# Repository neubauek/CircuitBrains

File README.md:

# CircuitBrains

## Deluxe
<br/>
https://kevinneubauer.com/projects/circuitbrains-deluxe/

Small form-factor 48-pin castellated pad module. Designed to allow an easy implementation of CircuitPython in maker/hacker projects without the bulk of a large breakout board.

Specs:
- Atmel ATSAMD51J19A Microcontroller (32-bit ARM Cortex M4)
- 8 MB SPI Flash
- Onboard 3.3V LDO Regulator
- Power and Status LEDs
- Breakouts for SPI and I2C
- Breakouts for 13 Analog and 19 Digital Inputs/Outputs

Revision History / Known Issues:

v1.0:
- Initial release
- Analog output does no work due to silicon issue with ATSAMD51. Requires a dedicated VREF/AREF pin with external 3.3 VREF input

v1.1 & v1.2:
- Not released due to issues resulting from design changes. I removed the pull-up on RST because the datasheet says it was optional. Turns out it was not so optional. These revisions will not function without a 10K resistor bodged onto the RST line.
- Dedicated a pin to VREF. Added a 0 Ohm resistor with a 3.3v input into VREF. 
- Switched from 4 layer to 2 layer board layout
- Rearranged layout to allow for pad documentation
- Added silkscreen for pad/pin assignments
- Added logo
- Removed inductor on VSW. Board will only work on linear power mode due to this.
- Removed polyfuse. Acceptable risk tradeoff for the space. If you want a fuse, add it to your design that incorporates this board.
- Removed Schottkey diode on VIN. Acceptable risk tradeoff for the space.
- Changed to a different flash chip with a smaller footprint
- Shuffled I/O pin assignments for more efficient trace routing/layout

v1.3:
- Added 10k pull-up back to RST.
- All tests working out: I2C, SPI, Analog & Digital In, Analog Out

## Basic
<br/>
https://kevinneubauer.com/projects/circuitbrains-basic/

Small form-factor 28-pin castellated pad module. Designed to allow an easy implementation of CircuitPython in maker/hacker projects without the bulk of a large breakout board.

Specs:
- Atmel ATSAMD21E18A Microcontroller (32-bit ARM Cortex M0)
- 4 MB SPI Flash
- Onboard 3.3V LDO Regulator
- Power and Status LEDs
- Breakouts for SPI and I2C
- Breakouts for 4 Analog and 8 Digital Inputs/Outputs

Revision History / Known Issues:
v1.2:
- Initial Release
- All tests working out

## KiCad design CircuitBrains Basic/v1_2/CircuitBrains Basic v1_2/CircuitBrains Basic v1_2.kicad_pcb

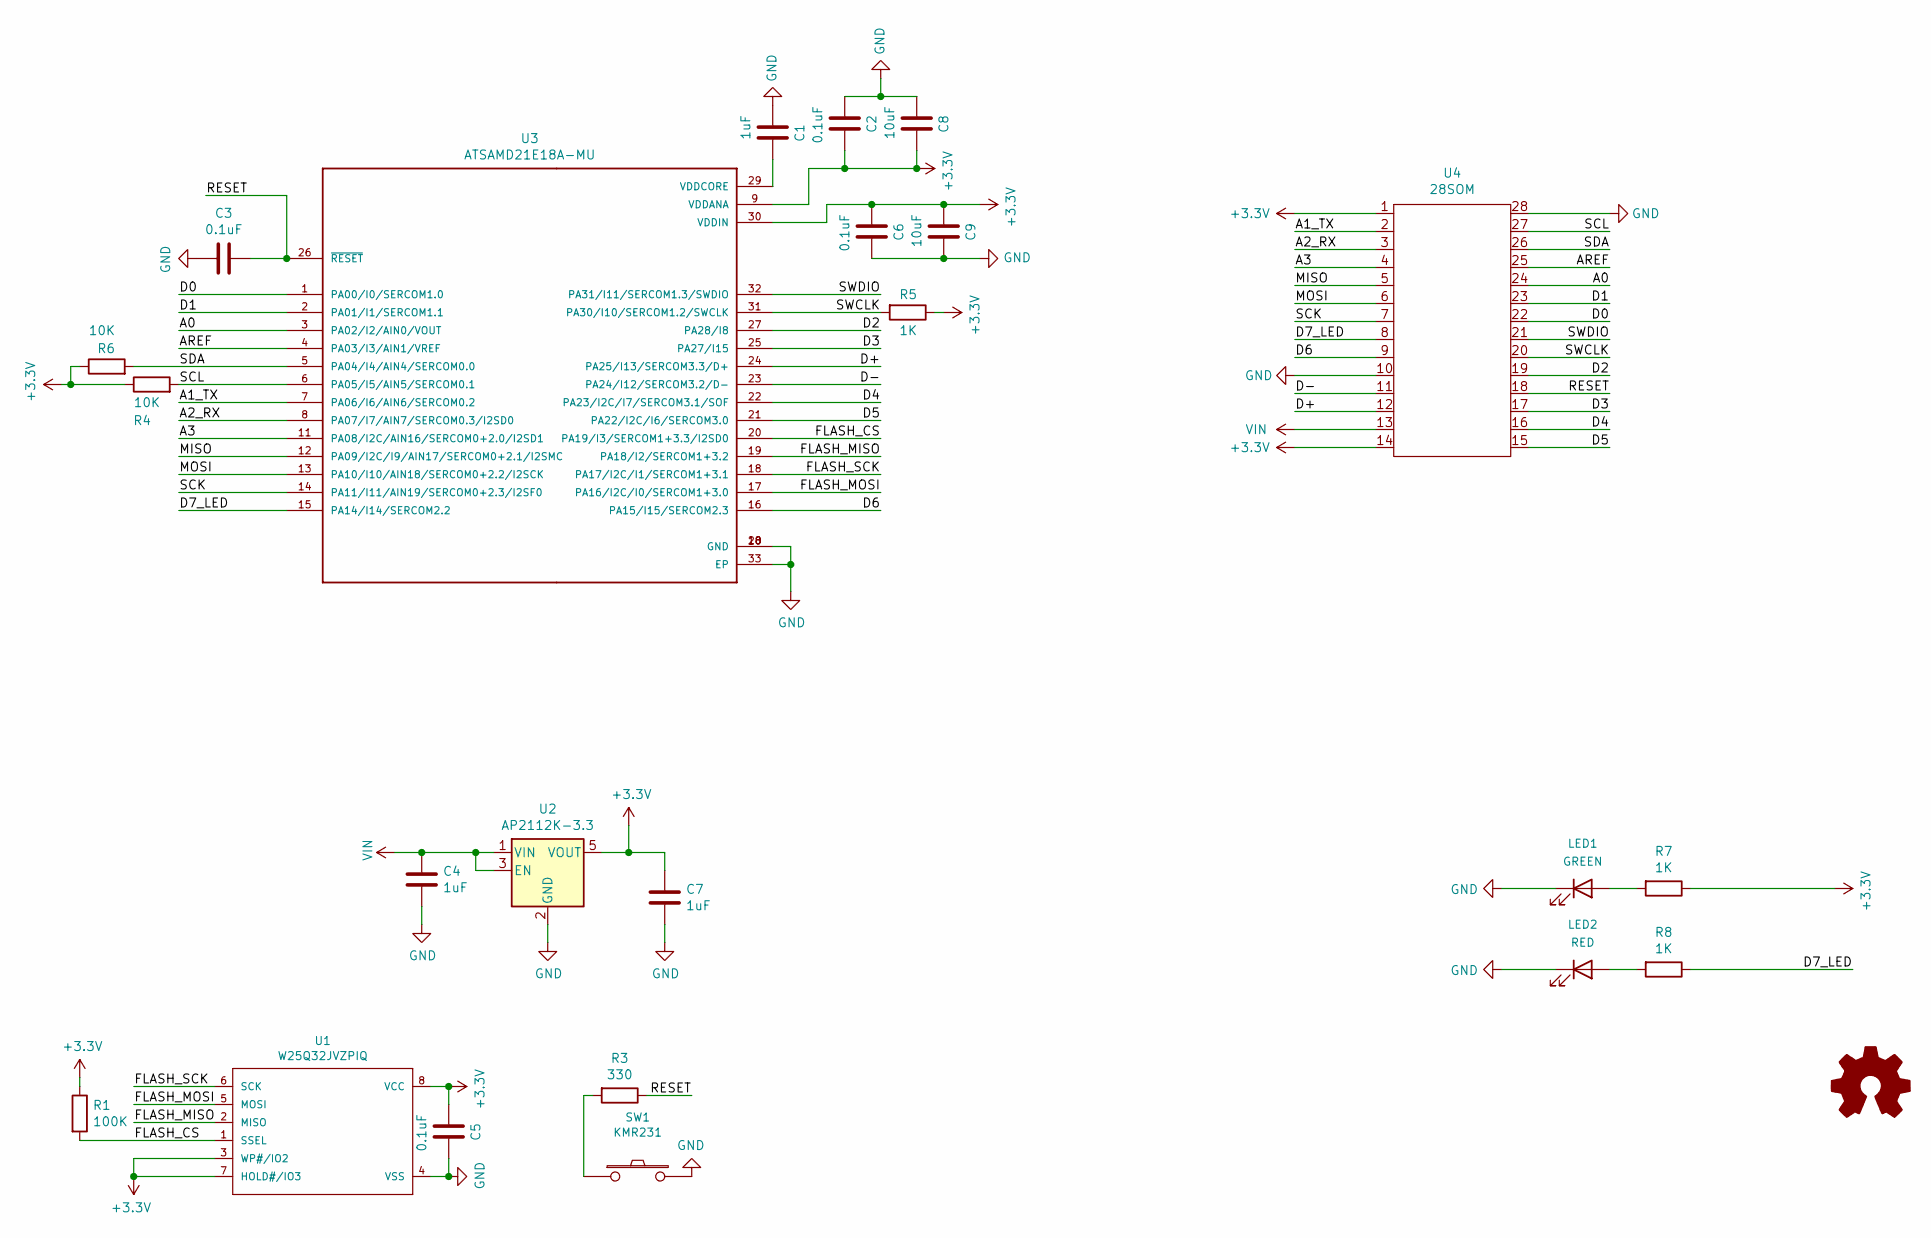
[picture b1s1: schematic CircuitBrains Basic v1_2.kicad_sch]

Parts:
C1, C4, C7: 1uF; C_0603_1608Metric
C2, C3, C5, C6: 0.1uF; C_0603_1608Metric
C8, C9: 10uF; C_0603_1608Metric
LED1: GREEN; LED_0603_1608Metric
LED2: RED; LED_0603_1608Metric
R1: 100K; R_0603_1608Metric
R3: 330; R_0603_1608Metric
R4, R6: 10K; R_0603_1608Metric
R5, R7, R8: 1K; R_0603_1608Metric
SW1: KMR231
U1: W25Q32JVZPIQ; WSON-8-1EP_6x5mm_P1.27mm_EP3.4x4.3mm
U2: AP2112K-3.3; SOT-23-5
U3: ATSAMD21E18A-MU; QFN50P500X500X100-33N
U4: 28SOM; 28SOM_25MMx25MM

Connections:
+3V3: C2.2, C5.1, C6.1, C7.1, C8.2, C9.1, R1.1, R4.1, R5.1, R6.1, R7.1, U1.3 (WP#/IO2), U1.7 (HOLD#/IO3), U1.8 (VCC), U2.5 (VOUT), U3.9 (VDDANA), U3.30 (VDDIN), U4.1, U4.14
/A0: U3.3 (PA02/I2/AIN0/VOUT), U4.24
/A1_TX: U3.7 (PA06/I6/AIN6/SERCOM0.2), U4.2
/A2_RX: U3.8 (PA07/I7/AIN7/SERCOM0.3/I2SD0), U4.3
/A3: U3.11 (PA08/I2C/AIN16/SERCOM0+2.0/I2SD1), U4.4
/AREF: U3.4 (PA03/I3/AIN1/VREF), U4.25
/D0: U3.1 (PA00/I0/SERCOM1.0), U4.22
/D1: U3.2 (PA01/I1/SERCOM1.1), U4.23
/D2: U3.27 (PA28/I8), U4.19
/D3: U3.25 (PA27/I15), U4.17
/D4: U3.22 (PA23/I2C/I7/SERCOM3.1/SOF), U4.16
/D5: U3.21 (PA22/I2C/I6/SERCOM3.0), U4.15
/D6: U3.16 (PA15/I15/SERCOM2.3), U4.9
/D7_LED: R8.1, U3.15 (PA14/I14/SERCOM2.2), U4.8
/D+: U3.24 (PA25/I13/SERCOM3.3/D+), U4.12
/D-: U3.23 (PA24/I12/SERCOM3.2/D-), U4.11
/FLASH_CS: R1.2, U1.1 (SSEL), U3.20 (PA19/I3/SERCOM1+3.3/I2SD0)
/FLASH_MISO: U1.2 (MISO), U3.19 (PA18/I2/SERCOM1+3.2)
/FLASH_MOSI: U1.5 (MOSI), U3.17 (PA16/I2C/I0/SERCOM1+3.0)
/FLASH_SCK: U1.6 (SCK), U3.18 (PA17/I2C/I1/SERCOM1+3.1)
/MISO: U3.12 (PA09/I2C/I9/AIN17/SERCOM0+2.1/I2SMC), U4.5
/MOSI: U3.13 (PA10/I10/AIN18/SERCOM0+2.2/I2SCK), U4.6
/RESET: C3.1, R3.1, U3.26 (~RESET~), U4.18
/SCK: U3.14 (PA11/I11/AIN19/SERCOM0+2.3/I2SF0), U4.7
/SCL: R4.2, U3.6 (PA05/I5/AIN5/SERCOM0.1), U4.27
/SDA: R6.2, U3.5 (PA04/I4/AIN4/SERCOM0.0), U4.26
/SWCLK: R5.2, U3.31 (PA30/I10/SERCOM1.2/SWCLK), U4.20
/SWDIO: U3.32 (PA31/I11/SERCOM1.3/SWDIO), U4.21
GND: C1.1, C2.1, C3.2, C4.2, C5.2, C6.2, C7.2, C8.1, C9.2, LED1.1 (K), LED2.1 (K), SW1.2, U1.4 (VSS), U2.2 (GND), U3.10 (GND), U3.28 (GND), U3.33 (EP), U4.10, U4.28
unnamed: C1.2, U3.29 (VDDCORE)
unnamed: LED1.2 (A), R7.2
unnamed: LED2.2 (A), R8.2
unnamed: R3.2, SW1.1
VIN: C4.1, U2.1 (VIN), U2.3 (EN), U4.13

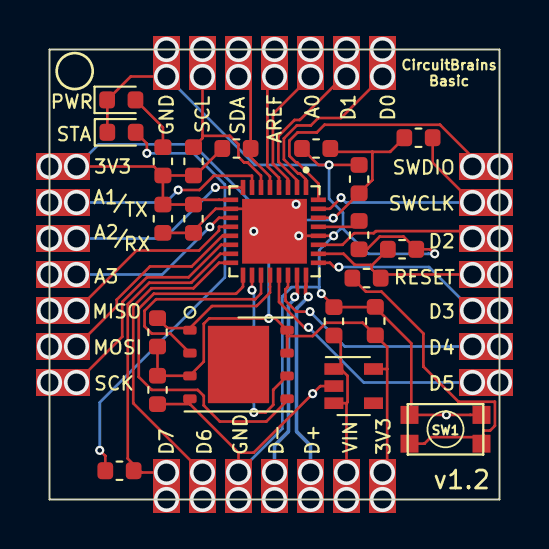
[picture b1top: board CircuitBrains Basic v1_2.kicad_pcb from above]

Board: 2 copper layers, 25.0 x 25.0 mm, 23 parts (0 on the bottom side), 34 nets.

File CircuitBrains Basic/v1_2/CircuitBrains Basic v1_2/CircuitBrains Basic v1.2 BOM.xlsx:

Reference(s) | Value | Manufacturer | Part | Qty
C1, C4, C7 | 1uF | Yageo | CC0603KRX5R8BB105 | 3
C2, C3, C5, C6 | 0.1uF | Yageo | CC0603JRX7R9BB104 | 4
C8, C9 | 10uF | Murata | GRM188R61E106KA73D | 2
LED1 | GREEN | Würth Elektronik | 150060VS75000 | 1
LED2 | RED | Würth Elektronik | 150060RS75000 | 1
R1 | 100K | Yageo | RC0603FR-07100KL | 1
R3 | 330 | Yageo | RC0603FR-07330RL | 1
R4, R6 | 10K | Yageo | RC0603FR-0710KL | 2
R5, R7, R8 | 1K | Yageo | RC0603FR-071KL | 3
SW1 | KMR231 | C&K | KMR231NG LFS | 1
U1 | W25Q32JVZPIQ | Winbond Electronics | W25Q32JVZPIQ | 1
U2 | AP2112K-3.3 | Diodes Incorporated | AP2112K-3.3TRG1 | 1
U3 | ATSAMD21E18A-MU | Microchip Technology | ATSAMD21E18A-MU | 1

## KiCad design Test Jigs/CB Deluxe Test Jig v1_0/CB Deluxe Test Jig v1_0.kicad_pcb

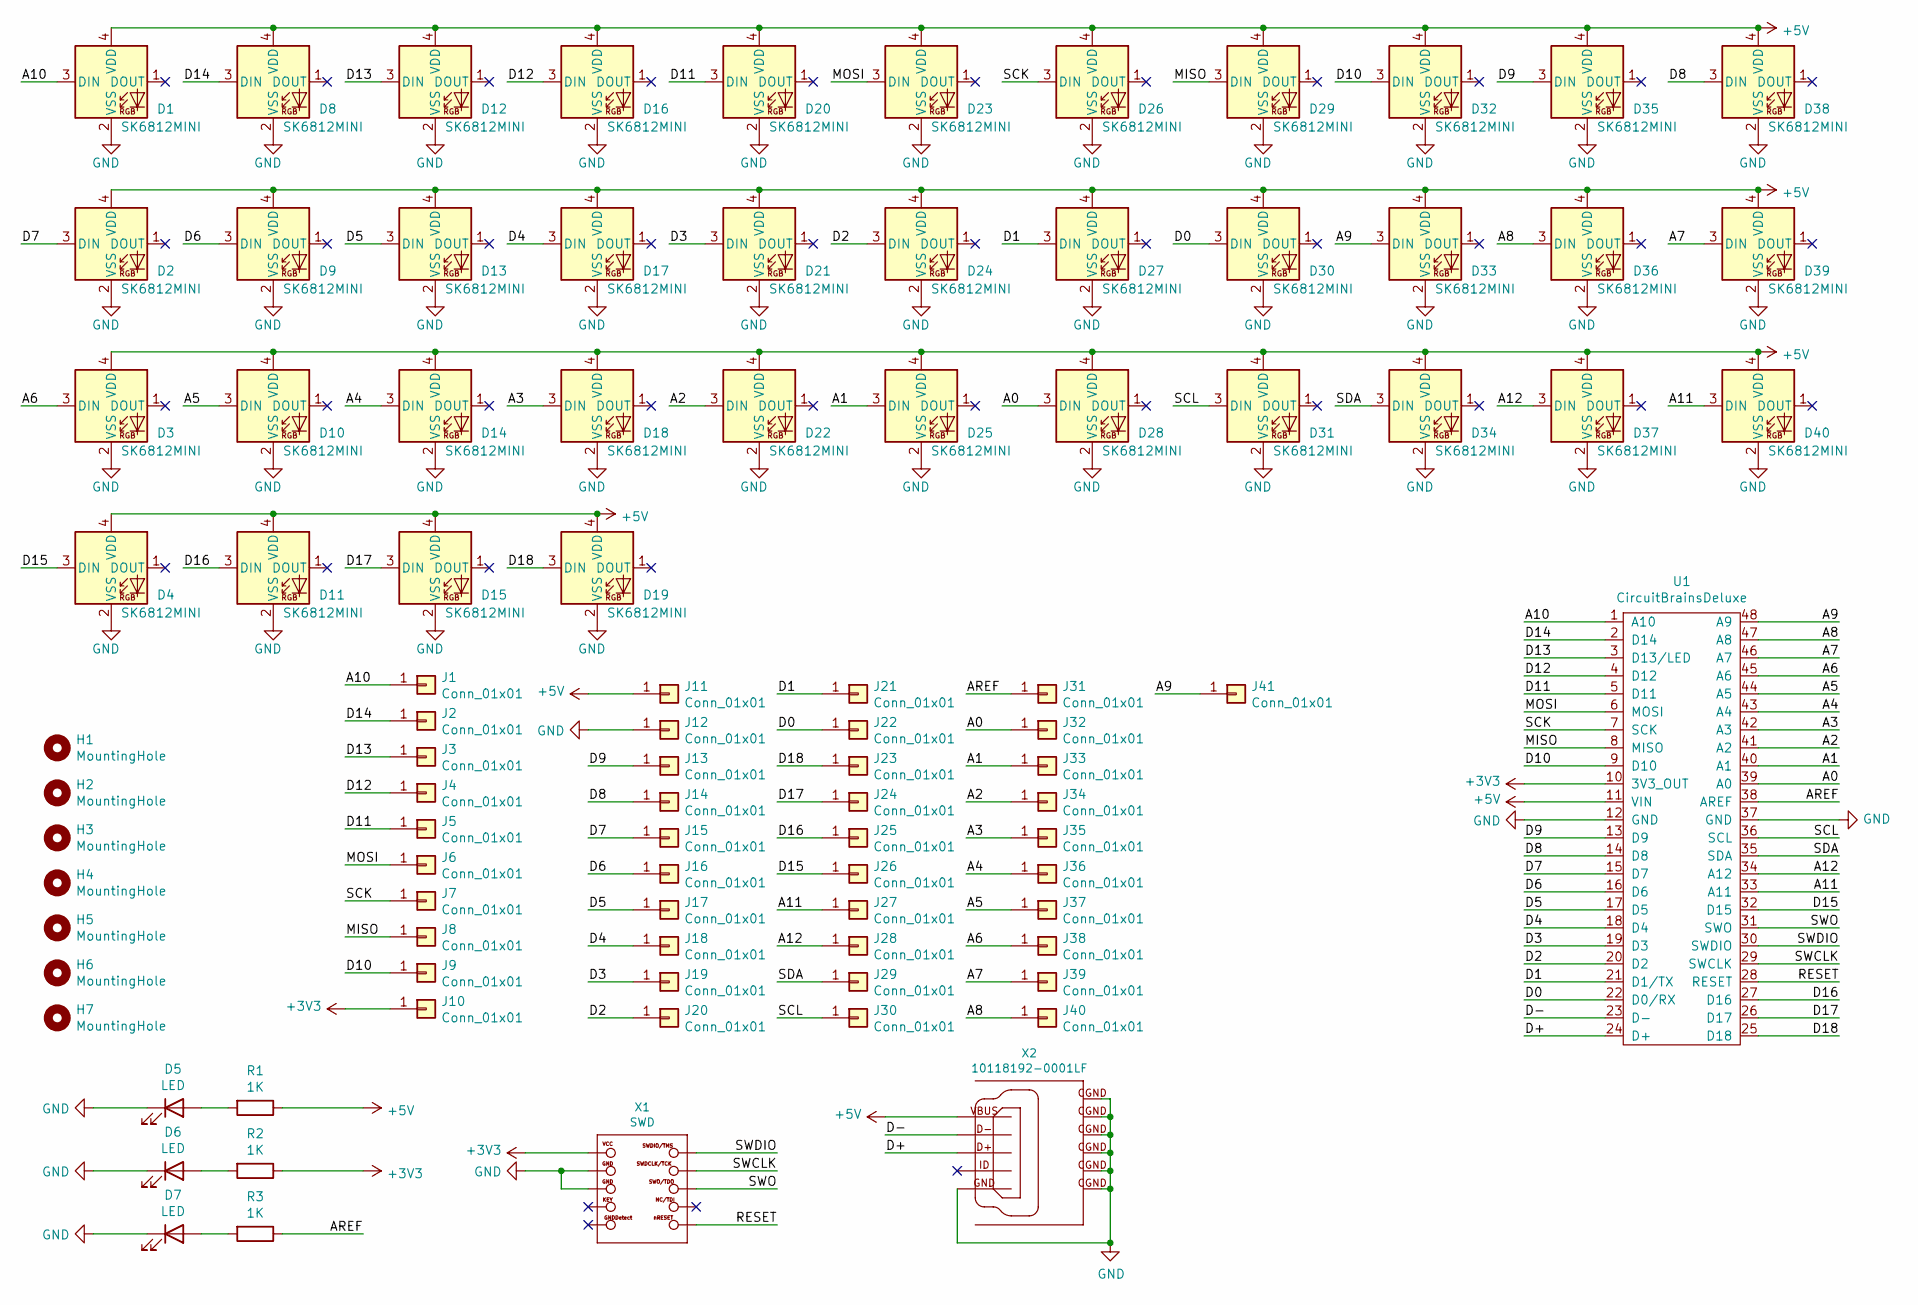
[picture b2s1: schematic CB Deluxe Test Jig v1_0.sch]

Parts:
D1, D2, D3, D4, D8, D9, D10, D11, D12, D13, D14, D15, D16, D17, D18, D19, D20, D21, D22, D23, D24, D25, D26, D27, D28, D29, D30, D31, D32, D33, D34, D35, D36, D37, D38, D39, D40: SK6812MINI; SK6812_Mini
D5, D6, D7: LED; LED_0805_2012Metric_Pad1.15x1.40mm_HandSolder
H1, H2, H3, H4, H5, H6, H7: MountingHole; MountingHole_3.2mm_M3
J1, J2, J3, J4, J5, J6, J7, J8, J9, J10, J11, J12, J13, J14, J15, J16, J17, J18, J19, J20, J21, J22, J23, J24, J25, J26, J27, J28, J29, J30, J31, J32, J33, J34, J35, J36, J37, J38, J39, J40, J41: Conn_01x01; PinHeader_1x01_P2.54mm_Vertical
R1, R2, R3: 1K; R_0805_2012Metric_Pad1.15x1.40mm_HandSolder
U1: CircuitBrainsDeluxe; Deluxe_48SOM_29MMx29MM_Pogo_Test_Jig
X1: SWD; 2X05_1.27MM_BOX_POSTS_SMT
X2: 10118192-0001LF; 10118192-0001LF(MICRO-USB-B-AMPHENOL-FCI)

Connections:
+3V3: J10.1, R2.1, U1.10 (3V3_OUT), X1.1 (VCC)
+5V: D1.4 (VDD), D2.4 (VDD), D3.4 (VDD), D4.4 (VDD), D8.4 (VDD), D9.4 (VDD), D10.4 (VDD), D11.4 (VDD), D12.4 (VDD), D13.4 (VDD), D14.4 (VDD), D15.4 (VDD), D16.4 (VDD), D17.4 (VDD), D18.4 (VDD), D19.4 (VDD), D20.4 (VDD), D21.4 (VDD), D22.4 (VDD), D23.4 (VDD), D24.4 (VDD), D25.4 (VDD), D26.4 (VDD), D27.4 (VDD), D28.4 (VDD), D29.4 (VDD), D30.4 (VDD), D31.4 (VDD), D32.4 (VDD), D33.4 (VDD), D34.4 (VDD), D35.4 (VDD), D36.4 (VDD), D37.4 (VDD), D38.4 (VDD), D39.4 (VDD), D40.4 (VDD), J11.1, R1.1, U1.11 (VIN), X2.VBUS
/A0: D28.3 (DIN), J32.1, U1.39 (A0)
/A1: D25.3 (DIN), J33.1, U1.40 (A1)
/A2: D22.3 (DIN), J34.1, U1.41 (A2)
/A3: D18.3 (DIN), J35.1, U1.42 (A3)
/A4: D14.3 (DIN), J36.1, U1.43 (A4)
/A5: D10.3 (DIN), J37.1, U1.44 (A5)
/A6: D3.3 (DIN), J38.1, U1.45 (A6)
/A7: D39.3 (DIN), J39.1, U1.46 (A7)
/A8: D36.3 (DIN), J40.1, U1.47 (A8)
/A9: D33.3 (DIN), J41.1, U1.48 (A9)
/A10: D1.3 (DIN), J1.1, U1.1 (A10)
/A11: D40.3 (DIN), J27.1, U1.33 (A11)
/A12: D37.3 (DIN), J28.1, U1.34 (A12)
/AREF: J31.1, R3.1, U1.38 (AREF)
/D0: D30.3 (DIN), J22.1, U1.22 (D0/RX)
/D1: D27.3 (DIN), J21.1, U1.21 (D1/TX)
/D2: D24.3 (DIN), J20.1, U1.20 (D2)
/D3: D21.3 (DIN), J19.1, U1.19 (D3)
/D4: D17.3 (DIN), J18.1, U1.18 (D4)
/D5: D13.3 (DIN), J17.1, U1.17 (D5)
/D6: D9.3 (DIN), J16.1, U1.16 (D6)
/D7: D2.3 (DIN), J15.1, U1.15 (D7)
/D8: D38.3 (DIN), J14.1, U1.14 (D8)
/D9: D35.3 (DIN), J13.1, U1.13 (D9)
/D10: D32.3 (DIN), J9.1, U1.9 (D10)
/D11: D20.3 (DIN), J5.1, U1.5 (D11)
/D12: D16.3 (DIN), J4.1, U1.4 (D12)
/D13: D12.3 (DIN), J3.1, U1.3 (D13/LED)
/D14: D8.3 (DIN), J2.1, U1.2 (D14)
/D15: D4.3 (DIN), J26.1, U1.32 (D15)
/D16: D11.3 (DIN), J25.1, U1.27 (D16)
/D17: D15.3 (DIN), J24.1, U1.26 (D17)
/D18: D19.3 (DIN), J23.1, U1.25 (D18)
/D+: U1.24 (D+), X2.D+
/D-: U1.23 (D-), X2.D-
/MISO: D29.3 (DIN), J8.1, U1.8 (MISO)
/MOSI: D23.3 (DIN), J6.1, U1.6 (MOSI)
/RESET: U1.28 (RESET), X1.10 (NRESET)
/SCK: D26.3 (DIN), J7.1, U1.7 (SCK)
/SCL: D31.3 (DIN), J30.1, U1.36 (SCL)
/SDA: D34.3 (DIN), J29.1, U1.35 (SDA)
/SWCLK: U1.29 (SWCLK), X1.4 (SWDCLK)
/SWDIO: U1.30 (SWDIO), X1.2 (SWDIO)
/SWO: U1.31 (SWO), X1.6 (SWO)
GND: D1.2 (VSS), D2.2 (VSS), D3.2 (VSS), D4.2 (VSS), D5.1 (K), D6.1 (K), D7.1 (K), D8.2 (VSS), D9.2 (VSS), D10.2 (VSS), D11.2 (VSS), D12.2 (VSS), D13.2 (VSS), D14.2 (VSS), D15.2 (VSS), D16.2 (VSS), D17.2 (VSS), D18.2 (VSS), D19.2 (VSS), D20.2 (VSS), D21.2 (VSS), D22.2 (VSS), D23.2 (VSS), D24.2 (VSS), D25.2 (VSS), D26.2 (VSS), D27.2 (VSS), D28.2 (VSS), D29.2 (VSS), D30.2 (VSS), D31.2 (VSS), D32.2 (VSS), D33.2 (VSS), D34.2 (VSS), D35.2 (VSS), D36.2 (VSS), D37.2 (VSS), D38.2 (VSS), D39.2 (VSS), D40.2 (VSS), J12.1, U1.12 (GND), U1.37 (GND), X1.3 (GND), X1.5 (GND), X2.CGND (SGND1), X2.GND
unnamed: D5.2 (A), R1.2
unnamed: D6.2 (A), R2.2
unnamed: D7.2 (A), R3.2

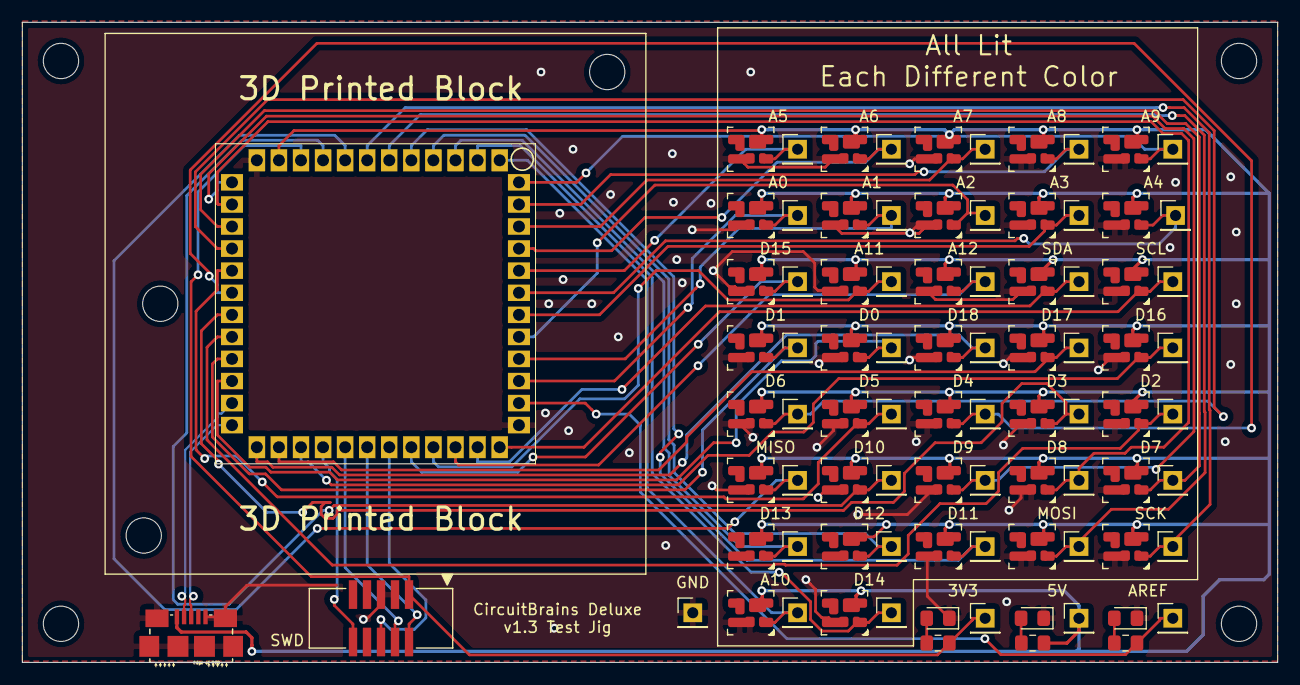
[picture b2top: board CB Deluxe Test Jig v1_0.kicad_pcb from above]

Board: 2 copper layers, 113.8 x 58.0 mm, 94 parts (0 on the bottom side), 50 nets.

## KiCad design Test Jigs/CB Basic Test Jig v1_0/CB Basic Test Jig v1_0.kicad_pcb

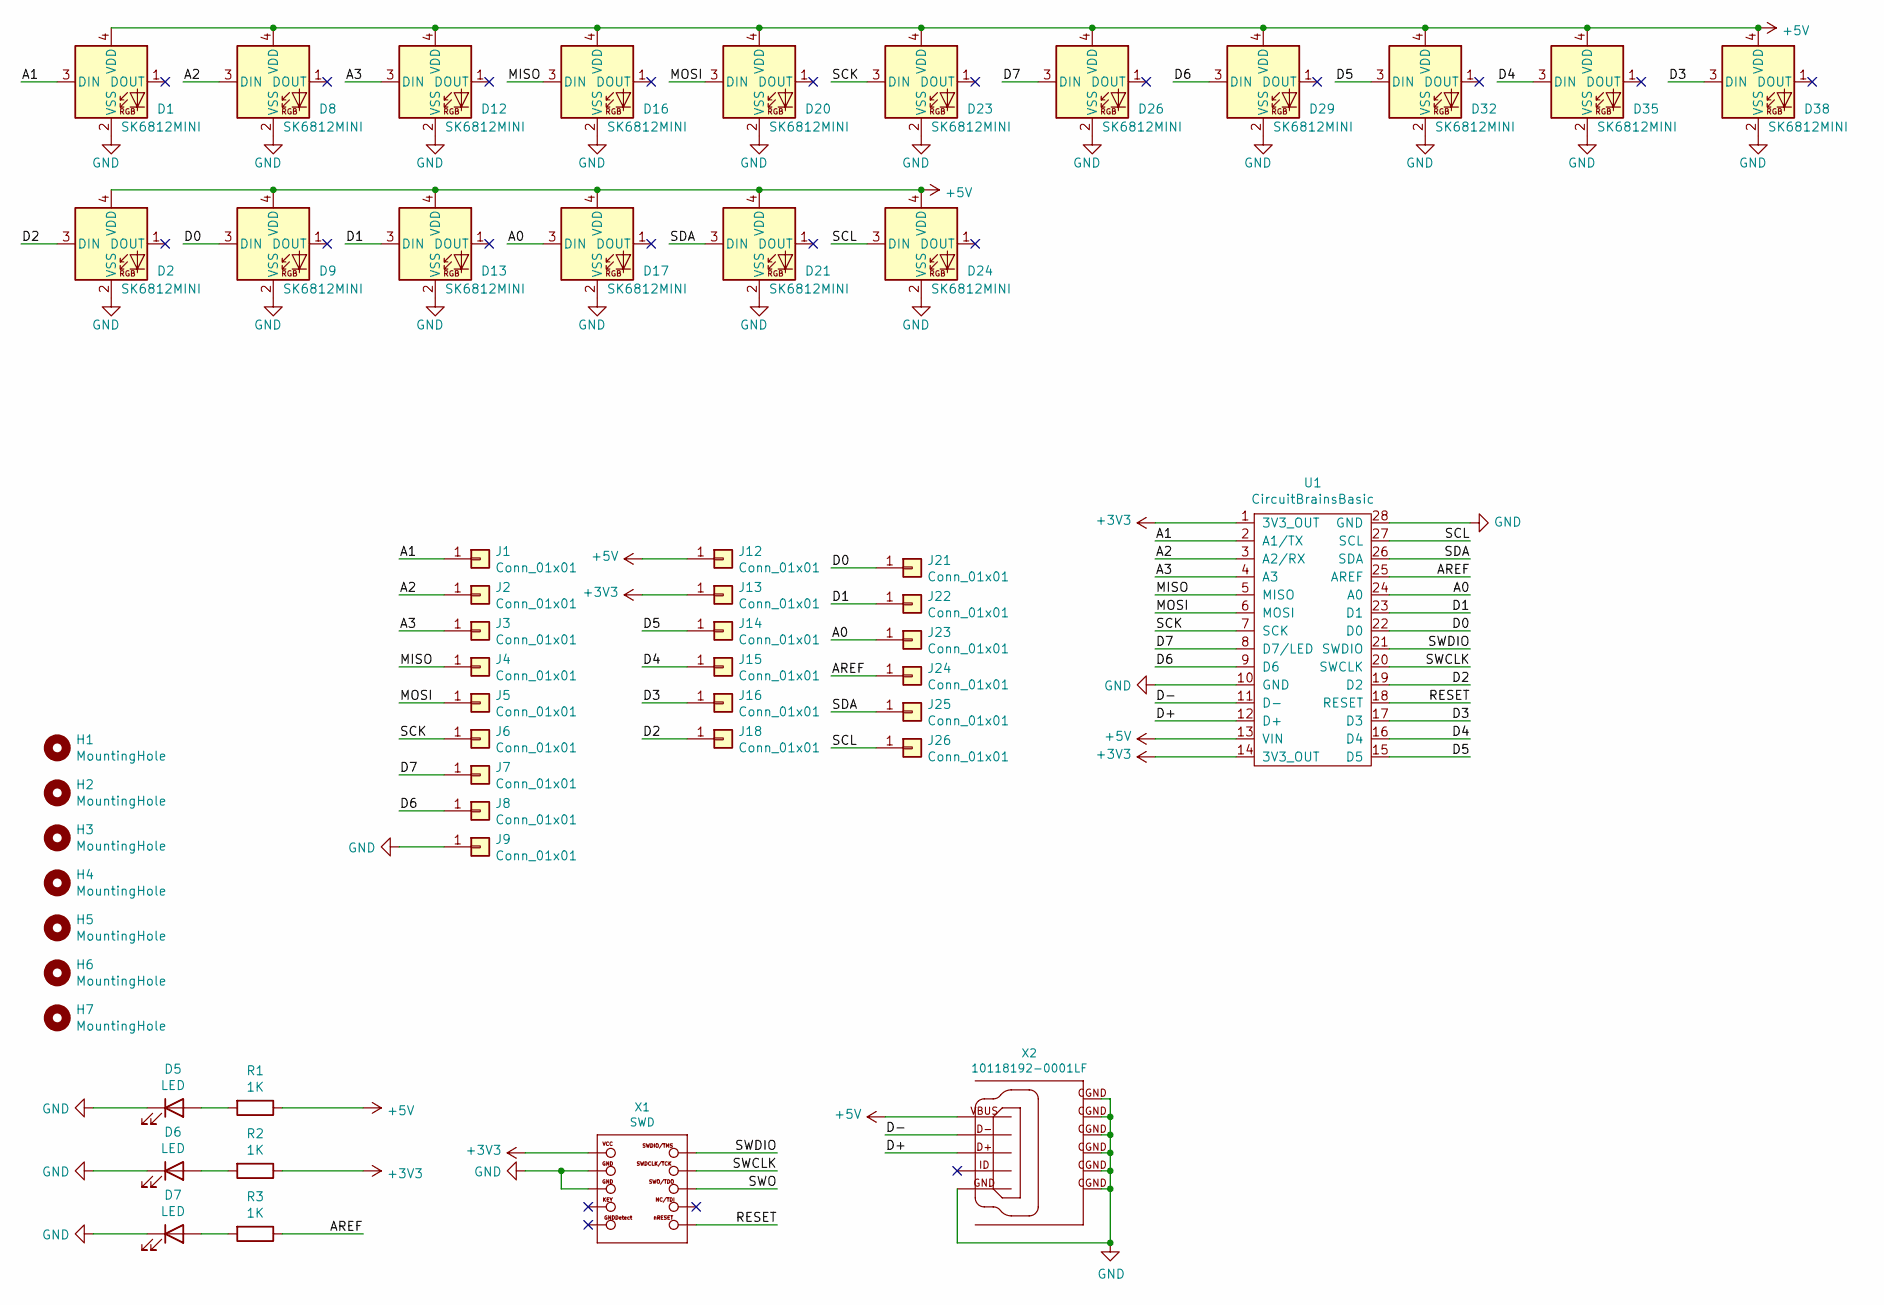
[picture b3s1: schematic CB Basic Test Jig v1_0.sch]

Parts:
D1, D2, D8, D9, D12, D13, D16, D17, D20, D21, D23, D24, D26, D29, D32, D35, D38: SK6812MINI; SK6812_Mini
D5, D6, D7: LED; LED_0805_2012Metric_Pad1.15x1.40mm_HandSolder
H1, H2, H3, H4, H5, H6, H7: MountingHole; MountingHole_3.2mm_M3
J1, J2, J3, J4, J5, J6, J7, J8, J9, J12, J13, J14, J15, J16, J18, J21, J22, J23, J24, J25, J26: Conn_01x01; PinHeader_1x01_P2.54mm_Vertical
R1, R2, R3: 1K; R_0805_2012Metric_Pad1.15x1.40mm_HandSolder
U1: CircuitBrainsBasic; Basic_28SOM_25MMx25MM_Pogo_Test_Jig
X1: SWD; 2X05_1.27MM_BOX_POSTS_SMT
X2: 10118192-0001LF; 10118192-0001LF(MICRO-USB-B-AMPHENOL-FCI)

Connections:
+3V3: J13.1, R2.1, U1.1 (3V3_OUT), U1.14 (3V3_OUT), X1.1 (VCC)
+5V: D1.4 (VDD), D2.4 (VDD), D8.4 (VDD), D9.4 (VDD), D12.4 (VDD), D13.4 (VDD), D16.4 (VDD), D17.4 (VDD), D20.4 (VDD), D21.4 (VDD), D23.4 (VDD), D24.4 (VDD), D26.4 (VDD), D29.4 (VDD), D32.4 (VDD), D35.4 (VDD), D38.4 (VDD), J12.1, R1.1, U1.13 (VIN), X2.VBUS
/A0: D17.3 (DIN), J23.1, U1.24 (A0)
/A1: D1.3 (DIN), J1.1, U1.2 (A1/TX)
/A2: D8.3 (DIN), J2.1, U1.3 (A2/RX)
/A3: D12.3 (DIN), J3.1, U1.4 (A3)
/AREF: J24.1, R3.1, U1.25 (AREF)
/D0: D9.3 (DIN), J21.1, U1.22 (D0)
/D1: D13.3 (DIN), J22.1, U1.23 (D1)
/D2: D2.3 (DIN), J18.1, U1.19 (D2)
/D3: D38.3 (DIN), J16.1, U1.17 (D3)
/D4: D35.3 (DIN), J15.1, U1.16 (D4)
/D5: D32.3 (DIN), J14.1, U1.15 (D5)
/D6: D29.3 (DIN), J8.1, U1.9 (D6)
/D7: D26.3 (DIN), J7.1, U1.8 (D7/LED)
/D+: U1.12 (D+), X2.D+
/D-: U1.11 (D-), X2.D-
/MISO: D16.3 (DIN), J4.1, U1.5 (MISO)
/MOSI: D20.3 (DIN), J5.1, U1.6 (MOSI)
/RESET: U1.18 (RESET), X1.10 (NRESET)
/SCK: D23.3 (DIN), J6.1, U1.7 (SCK)
/SCL: D24.3 (DIN), J26.1, U1.27 (SCL)
/SDA: D21.3 (DIN), J25.1, U1.26 (SDA)
/SWCLK: U1.20 (SWCLK), X1.4 (SWDCLK)
/SWDIO: U1.21 (SWDIO), X1.2 (SWDIO)
/SWO: X1.6 (SWO)
GND: D1.2 (VSS), D2.2 (VSS), D5.1 (K), D6.1 (K), D7.1 (K), D8.2 (VSS), D9.2 (VSS), D12.2 (VSS), D13.2 (VSS), D16.2 (VSS), D17.2 (VSS), D20.2 (VSS), D21.2 (VSS), D23.2 (VSS), D24.2 (VSS), D26.2 (VSS), D29.2 (VSS), D32.2 (VSS), D35.2 (VSS), D38.2 (VSS), J9.1, U1.10 (GND), U1.28 (GND), X1.3 (GND), X1.5 (GND), X2.CGND (SGND1), X2.GND
unnamed: D5.2 (A), R1.2
unnamed: D6.2 (A), R2.2
unnamed: D7.2 (A), R3.2

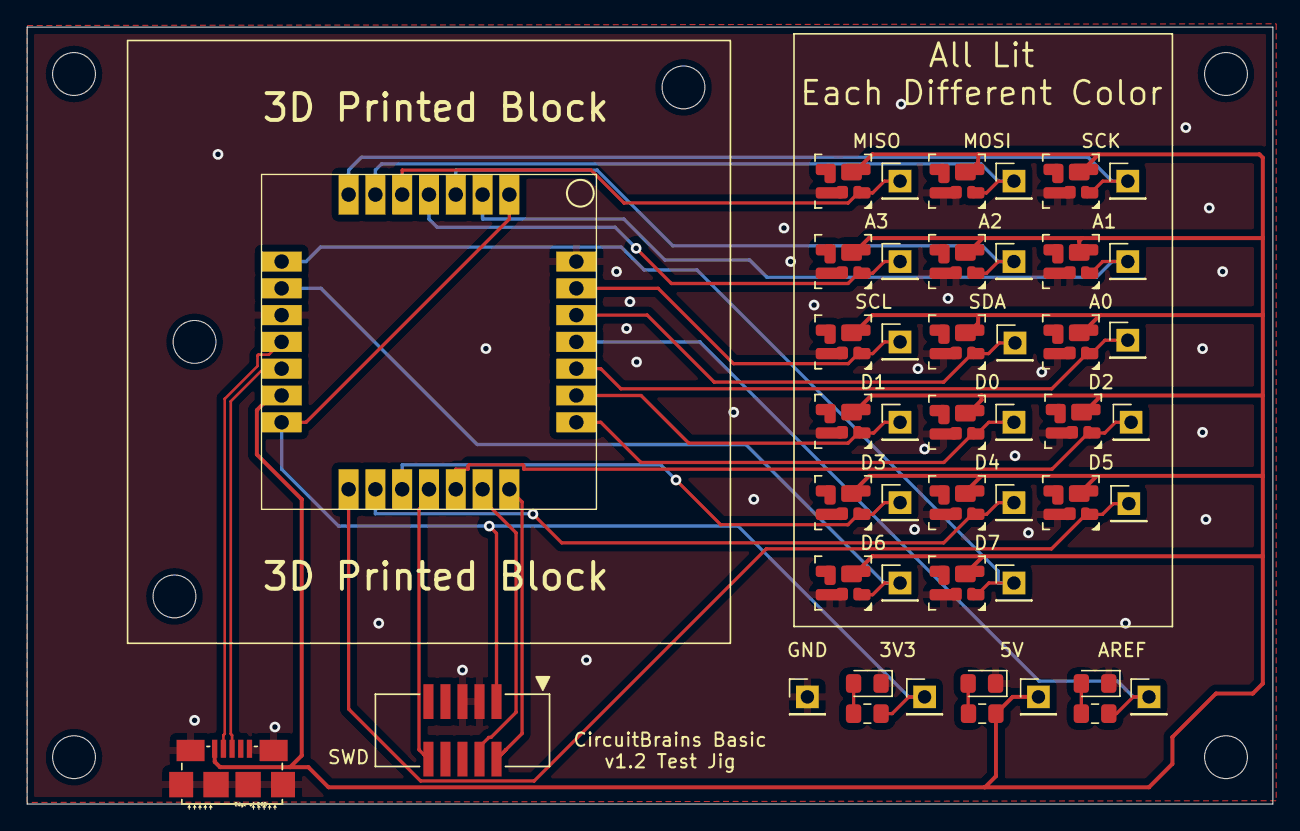
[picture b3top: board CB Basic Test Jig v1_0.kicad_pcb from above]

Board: 2 copper layers, 93.0 x 58.0 mm, 54 parts (0 on the bottom side), 29 nets.

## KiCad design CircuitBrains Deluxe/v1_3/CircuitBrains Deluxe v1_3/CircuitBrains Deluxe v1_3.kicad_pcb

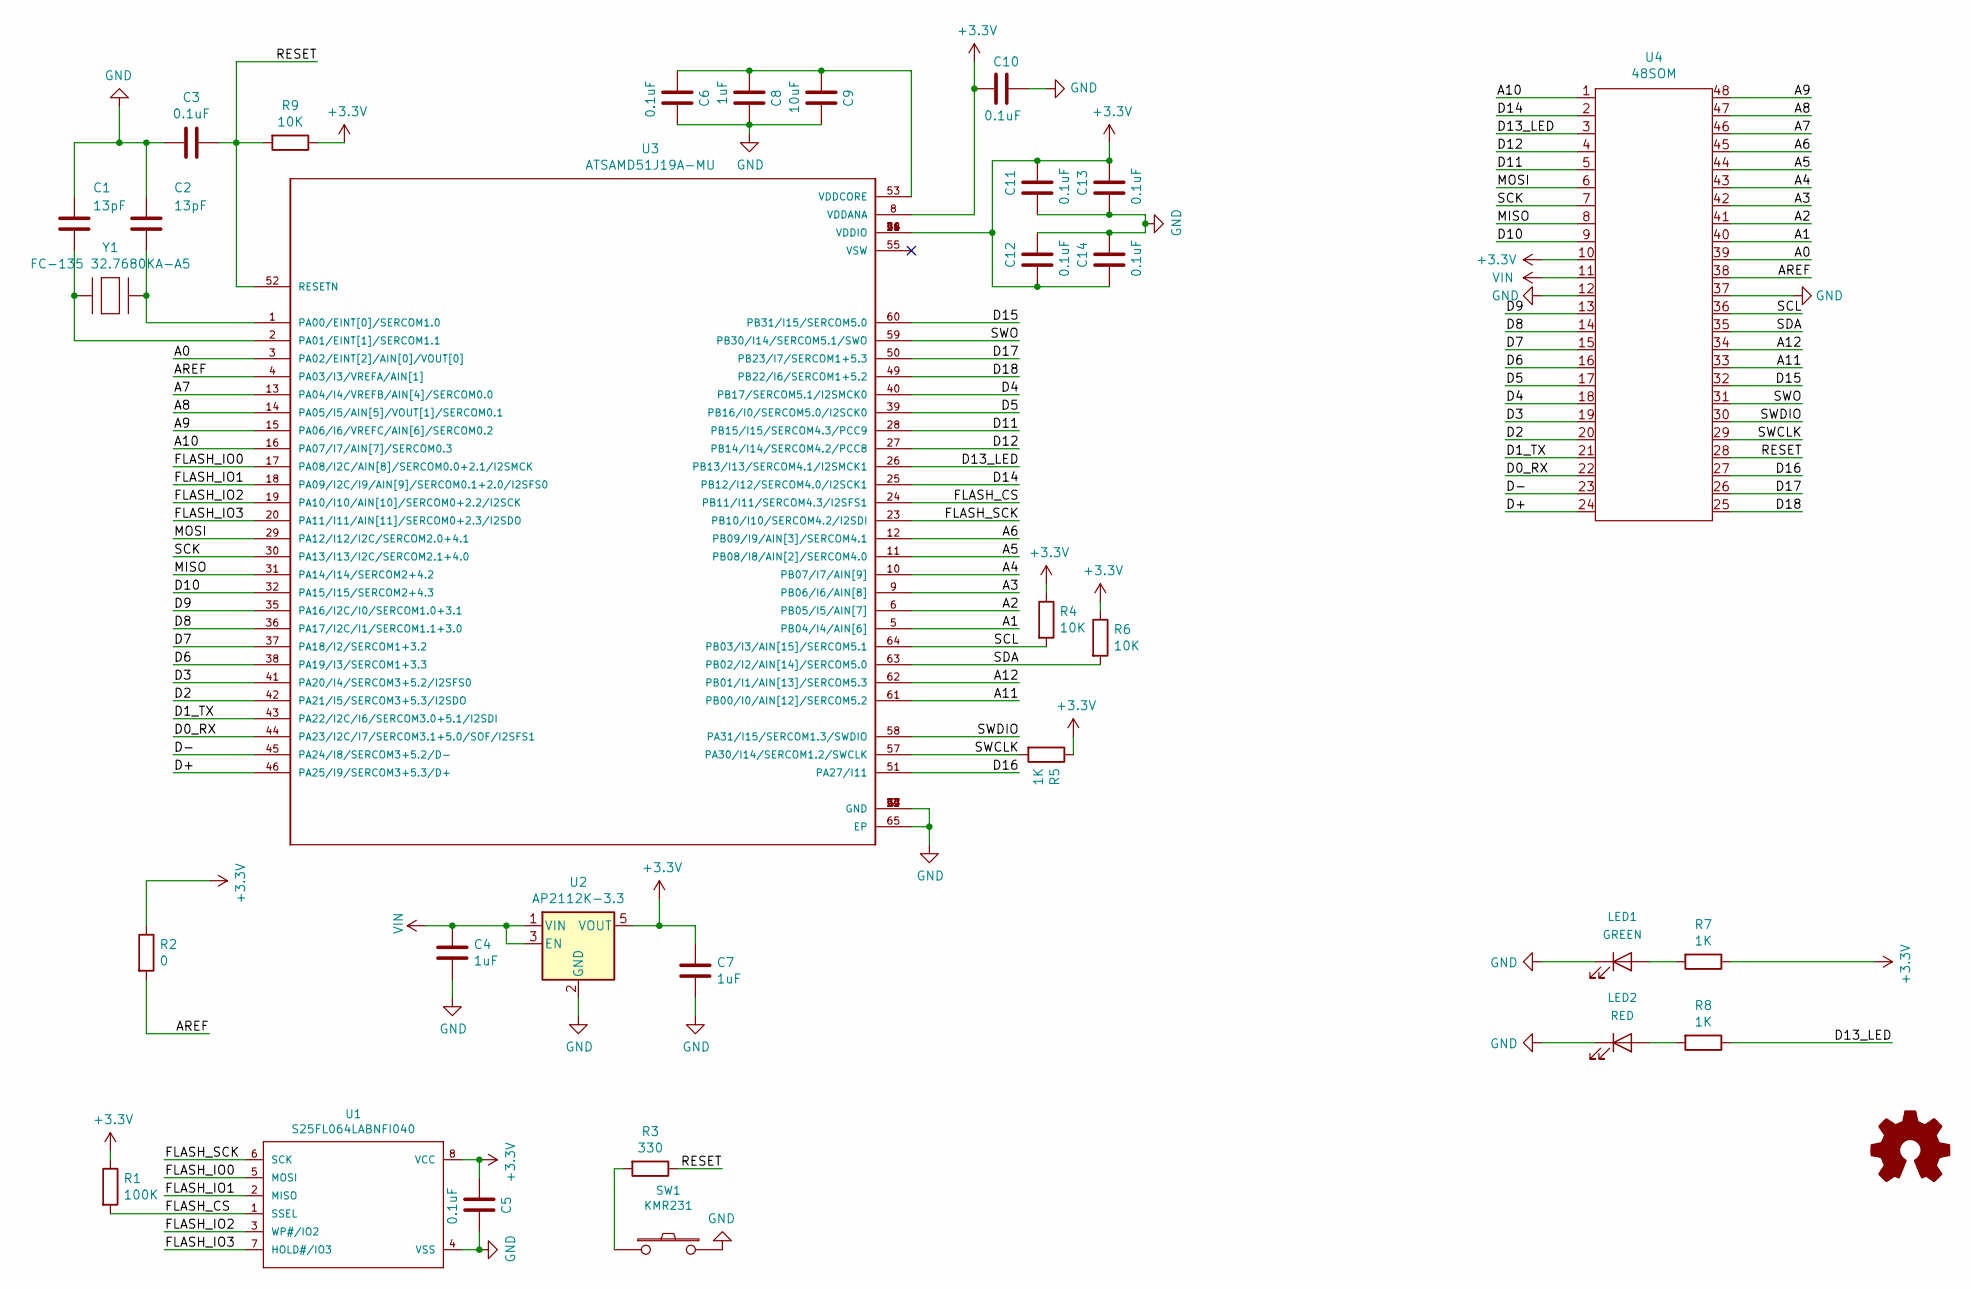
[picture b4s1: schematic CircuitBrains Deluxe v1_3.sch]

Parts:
C1, C2: 13pF; C_0603_1608Metric
C3, C5, C6, C10, C11, C12, C13, C14: 0.1uF; C_0603_1608Metric
C4, C7, C8: 1uF; C_0603_1608Metric
C9: 10uF; C_0603_1608Metric
LED1: GREEN; LED_0603_1608Metric
LED2: RED; LED_0603_1608Metric
R1: 100K; R_0603_1608Metric
R2: 0; R_0603_1608Metric
R3: 330; R_0603_1608Metric
R4, R6, R9: 10K; R_0603_1608Metric
R5, R7, R8: 1K; R_0603_1608Metric
SW1: KMR231
U1: S25FL064LABNFI040; WSON-8_4x4mm_P0.8mm
U2: AP2112K-3.3; SOT-23-5
U3: ATSAMD51J19A-MU; QFN64
U4: 48SOM; 48SOM_29MMx29MM
Y1: FC-135 32.7680KA-A5; XTAL3.2x1.5

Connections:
+3V3: C5.1, C7.1, C10.1, C11.2, C12.1, C13.2, C14.1, R1.1, R2.1, R4.1, R5.1, R6.1, R7.1, R9.1, U1.8 (VCC), U2.5 (VOUT), U3.8 (VDDANA), U3.21 (VDDIO), U3.34 (VDDIO), U3.48 (VDDIO), U3.56 (VDDIO), U4.10
/A0: U3.3 (PA02/EINT[2]/AIN[0]/VOUT[0]), U4.39
/A1: U3.5 (PB04/I4/AIN[6]), U4.40
/A2: U3.6 (PB05/I5/AIN[7]), U4.41
/A3: U3.9 (PB06/I6/AIN[8]), U4.42
/A4: U3.10 (PB07/I7/AIN[9]), U4.43
/A5: U3.11 (PB08/I8/AIN[2]/SERCOM4.0), U4.44
/A6: U3.12 (PB09/I9/AIN[3]/SERCOM4.1), U4.45
/A7: U3.13 (PA04/I4/VREFB/AIN[4]/SERCOM0.0), U4.46
/A8: U3.14 (PA05/I5/AIN[5]/VOUT[1]/SERCOM0.1), U4.47
/A9: U3.15 (PA06/I6/VREFC/AIN[6]/SERCOM0.2), U4.48
/A10: U3.16 (PA07/I7/AIN[7]/SERCOM0.3), U4.1
/A11: U3.61 (PB00/I0/AIN[12]/SERCOM5.2), U4.33
/A12: U3.62 (PB01/I1/AIN[13]/SERCOM5.3), U4.34
/AREF: R2.2, U3.4 (PA03/I3/VREFA/AIN[1]), U4.38
/D0_RX: U3.44 (PA23/I2C/I7/SERCOM3.1+5.0/SOF/I2SFS1), U4.22
/D1_TX: U3.43 (PA22/I2C/I6/SERCOM3.0+5.1/I2SDI), U4.21
/D2: U3.42 (PA21/I5/SERCOM3+5.3/I2SDO), U4.20
/D3: U3.41 (PA20/I4/SERCOM3+5.2/I2SFS0), U4.19
/D4: U3.40 (PB17/SERCOM5.1/I2SMCK0), U4.18
/D5: U3.39 (PB16/I0/SERCOM5.0/I2SCK0), U4.17
/D6: U3.38 (PA19/I3/SERCOM1+3.3), U4.16
/D7: U3.37 (PA18/I2/SERCOM1+3.2), U4.15
/D8: U3.36 (PA17/I2C/I1/SERCOM1.1+3.0), U4.14
/D9: U3.35 (PA16/I2C/I0/SERCOM1.0+3.1), U4.13
/D10: U3.32 (PA15/I15/SERCOM2+4.3), U4.9
/D11: U3.28 (PB15/I15/SERCOM4.3/PCC9), U4.5
/D12: U3.27 (PB14/I14/SERCOM4.2/PCC8), U4.4
/D13_LED: R8.1, U3.26 (PB13/I13/SERCOM4.1/I2SMCK1), U4.3
/D14: U3.25 (PB12/I12/SERCOM4.0/I2SCK1), U4.2
/D15: U3.60 (PB31/I15/SERCOM5.0), U4.32
/D16: U3.51 (PA27/I11), U4.27
/D17: U3.50 (PB23/I7/SERCOM1+5.3), U4.26
/D18: U3.49 (PB22/I6/SERCOM1+5.2), U4.25
/D+: U3.46 (PA25/I9/SERCOM3+5.3/D+), U4.24
/D-: U3.45 (PA24/I8/SERCOM3+5.2/D-), U4.23
/FLASH_CS: R1.2, U1.1 (SSEL), U3.24 (PB11/I11/SERCOM4.3/I2SFS1)
/FLASH_IO0: U1.5 (MOSI), U3.17 (PA08/I2C/AIN[8]/SERCOM0.0+2.1/I2SMCK)
/FLASH_IO1: U1.2 (MISO), U3.18 (PA09/I2C/I9/AIN[9]/SERCOM0.1+2.0/I2SFS0)
/FLASH_IO2: U1.3 (WP#/IO2), U3.19 (PA10/I10/AIN[10]/SERCOM0+2.2/I2SCK)
/FLASH_IO3: U1.7 (HOLD#/IO3), U3.20 (PA11/I11/AIN[11]/SERCOM0+2.3/I2SDO)
/FLASH_SCK: U1.6 (SCK), U3.23 (PB10/I10/SERCOM4.2/I2SDI)
/MISO: U3.31 (PA14/I14/SERCOM2+4.2), U4.8
/MOSI: U3.29 (PA12/I12/I2C/SERCOM2.0+4.1), U4.6
/RESET: C3.1, R3.1, R9.2, U3.52 (RESETN), U4.28
/SCK: U3.30 (PA13/I13/I2C/SERCOM2.1+4.0), U4.7
/SCL: R4.2, U3.64 (PB03/I3/AIN[15]/SERCOM5.1), U4.36
/SDA: R6.2, U3.63 (PB02/I2/AIN[14]/SERCOM5.0), U4.35
/SWCLK: R5.2, U3.57 (PA30/I14/SERCOM1.2/SWCLK), U4.29
/SWDIO: U3.58 (PA31/I15/SERCOM1.3/SWDIO), U4.30
/SWO: U3.59 (PB30/I14/SERCOM5.1/SWO), U4.31
GND: C1.1, C2.1, C3.2, C4.2, C5.2, C6.2, C7.2, C8.2, C9.2, C10.2, C11.1, C12.2, C13.1, C14.2, LED1.1 (K), LED2.1 (K), SW1.2, U1.4 (VSS), U2.2 (GND), U3.7 (GND), U3.22 (GND), U3.33 (GND), U3.47 (GND), U3.54 (GND), U3.65 (EP), U4.12, U4.37
unnamed: C1.2, U3.2 (PA01/EINT[1]/SERCOM1.1), Y1.P$1
unnamed: C2.2, U3.1 (PA00/EINT[0]/SERCOM1.0), Y1.P$2
unnamed: C6.1, C8.1, C9.1, U3.53 (VDDCORE)
unnamed: LED1.2 (A), R7.2
unnamed: LED2.2 (A), R8.2
unnamed: R3.2, SW1.1
VIN: C4.1, U2.1 (VIN), U2.3 (EN), U4.11

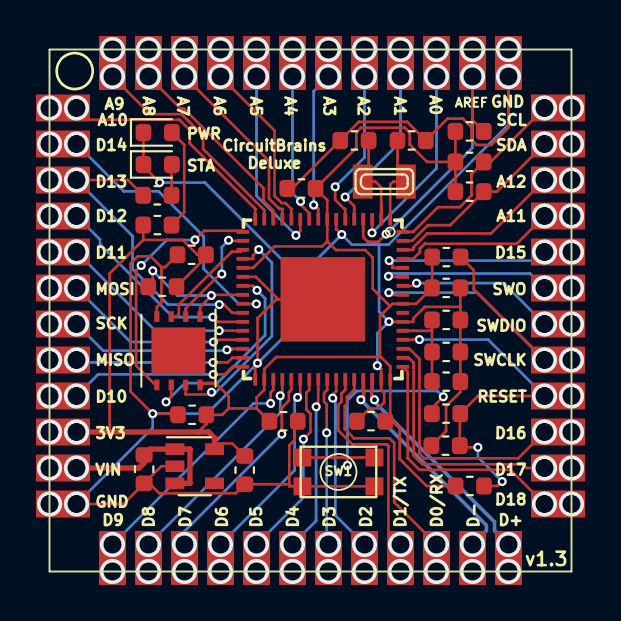
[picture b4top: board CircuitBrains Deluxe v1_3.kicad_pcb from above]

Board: 2 copper layers, 29.0 x 29.0 mm, 31 parts (0 on the bottom side), 59 nets.

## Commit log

2019-12-12 Added CircuitBrains Deluxe v1_0 Project, Library and Footprints
2019-12-12 Remove .DS_Store files
2019-12-30 Added v1.3 Schematic and Board
2019-12-30 Fix & footprint/library
    Fixed a deleted reference in kicad project file
    Added kicad footprint and library files for the module
2019-12-30 Added Interactive BOM
2020-01-15 Updated Readme with CB Deluxe graphics
2020-01-15 Updated Readme and image
2020-01-18 Fixed silk label size on board
2020-02-24 Removed Deluxe 1.0
2020-03-12 Added Test Jigs
2020-03-13 Added CircuitBrains Basic
2020-04-08 Added Eagle libraries
2020-12-04 Updated docs & updated CB Basic board file to kicad 6 format
2020-12-04 Fixed readme
2023-05-31 Fixed links in README
